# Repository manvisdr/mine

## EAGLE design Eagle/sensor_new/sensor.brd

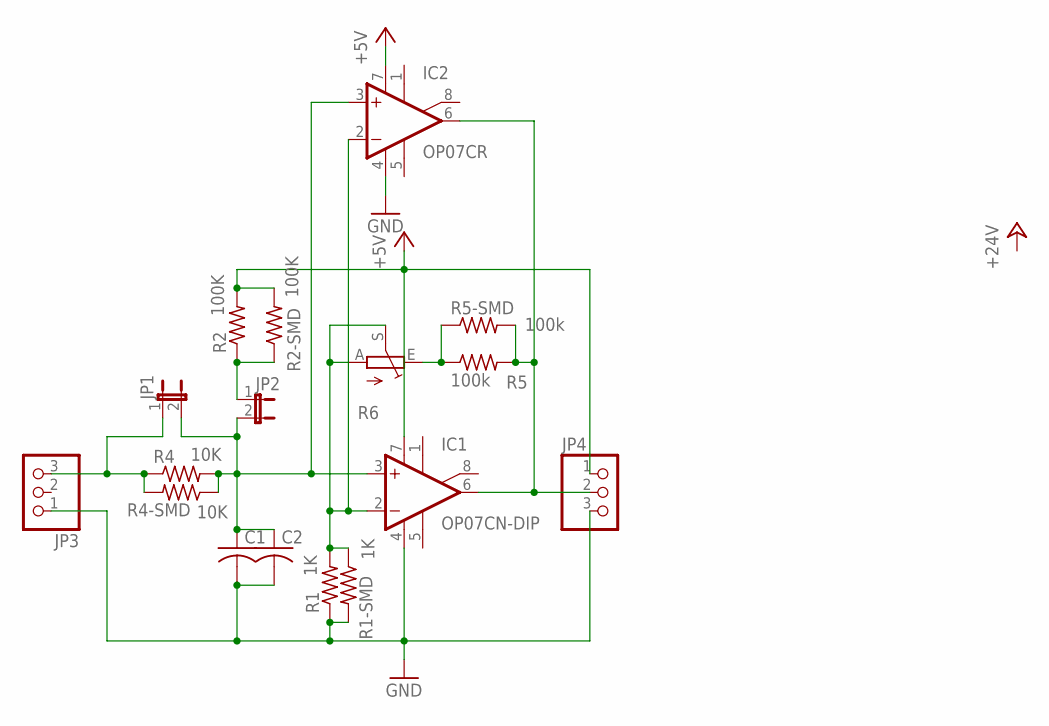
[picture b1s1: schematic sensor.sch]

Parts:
C1: C-US025-030X050; C025-030X050
C2: C-USC0805; C0805
IC1: OP07CN-DIP; DIL08
IC2: OP07CR; SO08
JP1, JP2: JP1E; JP1
JP3, JP4: PINHD-1X3; 1X03
R1: 1K; 0204/5
R1-SMD: 1K; R0805
R2: 100K; 0204/5
R2-SMD: 100K; R0805
R4: 10K; 0204/5
R4-SMD: 10K; R0805
R5: 100k; 0204/5
R5-SMD: 100k; R0805
R6: TRIM_EU-B64Y; B64Y

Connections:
+5V: IC1.7 (V+), IC2.7 (V+), JP4.1, R2.2, R2-SMD.2
GND: C1.2, C2.2, IC1.4 (V-), IC2.4 (V-), JP3.1, JP4.3, R1.1, R1-SMD.2
unnamed: IC1.2 (-IN), IC2.2 (-IN), R1.2, R1-SMD.1, R6.A, R6.S
unnamed: C1.1, C2.1, IC1.3 (+IN), IC2.3 (+IN), JP1.2, JP2.2, R4.2, R4-SMD.1
unnamed: JP1.1, JP3.3, R4.1, R4-SMD.2
unnamed: JP2.1, R2.1, R2-SMD.1
unnamed: R5.1, R5-SMD.1, R6.E
unnamed: IC1.6 (OUT), IC2.6 (OUT), JP4.2, R5.2, R5-SMD.2

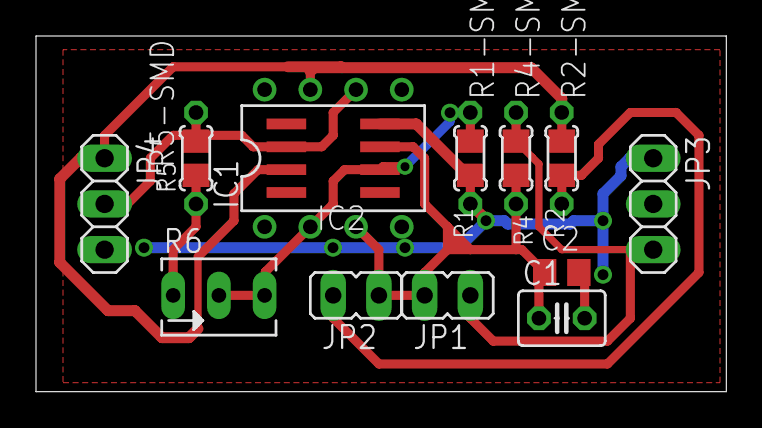
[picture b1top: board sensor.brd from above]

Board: 2 copper layers, 38.4 x 19.8 mm, 17 parts (0 on the bottom side), 8 nets.

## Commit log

2022-03-20 Create aa
